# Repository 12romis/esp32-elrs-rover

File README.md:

# ESP32-ELRS-Rover

Ровер на ESP32-S3 (YD-ESP32-S3 N16R8) з керуванням через ExpressLRS/CRSF. ESP-IDF v6.1, C. Танковий привід: два борти по два колеса,
енкодери на кожному колесі, регулятор швидкості бортів, чотири далекоміри VL53L0X, світло, зумер, вбудований RGB-індикатор плати.

## Що вміє ровер

- Їде за правим стіком пульта (тяга й поворот), озброюється тумблером (канал 5), тримає швидкість бортів регулятором.
- Зупиняється при втраті звʼязку довше за 0.5 с, при напрузі акумулятора нижче 6.0 В і перед перешкодою (стан OBSTACLE_HOLD).
- Повертає на пульт напругу акумулятора (телеметрія) і показує стан утримання звуком, кольором індикатора й блиманням світла.
- Тумблер CH9 вмикає й вимикає контроль перешкод; зеленуватий індикатор плати показує, що контроль ввімкнений і реально охороняє.
- Після кожної сесії (озброєння → вихід з руху) надсилає на сервер власника звіт (JSON, MQTT поверх TLS) лише в DISARMED; невдалі
  звіти (до двох) зберігаються в пам'яті плати.
- Консоль через USB: стан, команди руху (стендовий режим), світло, зумер, енкодери, регулятор, далекоміри, звіти.

## Структура репозиторію

- `docs/` — контекст заліза й прошивки (`01-ASSEMBLY-BRINGUP.md`, `02-FIRMWARE-CONTEXT.md`), конституція (`constitution.md`),
  журнал вимірювань (`measured.md`), блок-схема (`architecture.md`), чекліст самоперевірки (`self-check.md`), дорожня карта
  (`roadmap.md`), специфікації фаз у `docs/features/<фаза>/`.
- `kicad-rover/` — схема й плата (лише читання).
- `main/`, `components/` — прошивка. Кожен компонент ділиться на `<name>_core.c` (чиста логіка, без ESP-IDF) і `<name>_hal.c`.
- `test/host/` — хостові тести чистої логіки і перевірки правил проєкту.
- `tools/bringup/` — діагностичні прошивки P0–P7 (результати — у `docs/measured.md`).

Усі номери ліній GPIO — лише в `components/board/include/board_pins.h`.

## Збірка, прошивка, тести

Збірка (потрібне середовище ESP-IDF v6.1):

```bash
source ~/.espressif/tools/activate_idf_v6.1.sh
idf.py build
```

Прошивку на плату робить Розробник через розширення ESP-IDF у VS Code (ціль `esp32s3`); агент лише збирає. Після прошивки відкрити
монітор, консоль відповідає на `help`.

Хостові тести й перевірки правил (звичайний gcc, без плати):

```bash
test/host/run_tests.sh
```

Опис перевірок — у `test/host/README.md`. Перевірки з правками захищених файлів на гілці фази: `ALLOW_PROTECTED=1 test/host/check_protected.sh`.

## Інтерфейси

### Консоль (USB)

Повний список — команда `help`. Права команд залежать від стану автомата (`status` показує стан і історію переходів).

| Команда | Призначення |
|---|---|
| `help`, `status` | довідка; стан, час роботи, пам'ять, причина скидання, сховище, світло, індикатор, пульт, **час кроку керування**, енкодери, історія переходів |
| `arm`, `drive <тяга> <поворот>` | озброєння і рух (`drive` діє 2 с) — з консолі лише в стендовому режимі, до появи пульта |
| `disarm` | роззброєння — у будь-якому стані |
| `light`, `beep` | світло й зумер: `light` у DISARMED (в ARMED лише `light head`), `beep` у DISARMED і ARMED; в OBSTACLE_HOLD обидві відхиляються |
| `enc [reset]` | знімок енкодерів |
| `pid ...` | регулятор швидкості бортів |
| `tof [reinit]` | далекоміри, сектори, поріг; `reinit` лише в DISARMED |
| `report` | звіти сесій: черга (до двох), режим контролю перешкод, мережа; у DISARMED запускає спробу передачі негайно, в інших станах лише показує стан. Пароль і SSID не друкуються: «задано / не задано» |
| `reboot`, `wdt-test` | службові (лише в безпечних станах) |

### Пульт

Канали CRSF: 1 — поворот, 2 — тяга, 5 — ARM/DISARM (тумблер), **9 — режим контролю перешкод** (див. нижче), 8 — трипозиційний перемикач, за P5 призначений під фари (у прошивці поки не використовується; докладно: `docs/02-FIRMWARE-CONTEXT.md` §1.3 і `docs/measured.md`).

**CH9 — контроль перешкод.** Значення каналу вище середини (> 992) — контроль **увімкнено**, інакше — **вимкнено** (далекоміри лише міряють,
ровер не зупиняється перед перешкодою; відсічка по напрузі, втрата зв'язку, STBY, I²C діють без змін). Поки пульт не передав
кадр або зв'язок втрачено — контроль **увімкнено** (`status` пише «за замовчуванням, пульт не підтвердив»). У мікшері EdgeTX
виведіть вибраний тумблер (SB, SC, SE чи SF) на канал CH9. Два положення цього тумблера **ще не виміряні**: Розробник записує їх у
`docs/measured.md` (spec OQ-6); до заміру канал без призначеного тумблера стоїть на 992 і вимикає захист.

### Телеметрія на пульт

Раз на 200 мс ровер надсилає кадр датчика батареї CRSF: **напруга з розв'язністю 0.1 В**. **Струм, ємність і відсоток заряду нульові
й означають «немає даних»** (датчиків немає): пульт може показувати «0 А» чи «0 %» — це не вимір. Якщо свіжого виміру напруги немає,
кадр не надсилається. На пульті датчик має знайтися автоматично (на модулі передавача співвідношення телеметрії не «вимкнено»).

### Індикація станів

| Стан | Зумер | Індикатор плати | Світло |
|---|---|---|---|
| DISARMED | короткий сигнал на вході | **зеленуватий**, якщо контроль перешкод ввімкнений і хоч один далекомір охороняє; інакше погашений | задні ліхтарі червоні, фари вручну |
| ARMED | короткий сигнал на вході | те саме (зеленуватий лише за ввімкненого контролю й охорони) | фари автоматично, задні ліхтарі: жовтий уперед, зелений назад |
| OBSTACLE_HOLD | подвійний біп на вході; на виході в ARMED — один сигнал 200 мс | **жовтий** | передній сектор зайнятий — блимають фари; задній — блимають задні ліхтарі |
| FAILSAFE | сигнал на вході, писк кожні 2 с | червоний | задні ліхтарі блимають червоним |

Пріоритет кольорів: червоний (FAILSAFE) > жовтий (OBSTACLE_HOLD) > зеленуватий > погашений. У BOOT, SELFTEST і FAULT індикатор
погашений. Консоль при вході в утримання називає **кожен** датчик сектора, що бачить перешкоду, з відстанню.

### Звіт сесії

Сесія — від озброєння до виходу з ARMED/OBSTACLE_HOLD у DISARMED чи FAILSAFE. Після неї ровер у DISARMED вмикає Wi-Fi лише на
коротку спробу (до 30 с), публікує один JSON-звіт на сервер (`rover/<mac>/session`, QoS 1) і одразу вимикає Wi-Fi. Озброєння
перериває спробу. Якщо доставити не вдалось, до двох останніх звітів лежать у пам'яті плати (переживають перезапуск, зокрема FAILSAFE
через напругу) і йдуть при наступному DISARMED або командою `report`. Поля звіту — [contracts/events.md](docs/features/phase8-session-report/contracts/events.md).

Налаштування мережі (**секрети не потрапляють у git**):

1. Скопіюйте `components/report/report_secrets.example.h` у `components/report/report_secrets.h` (файл у `.gitignore`) і заповніть
   SSID та пароль Wi-Fi, адресу й порт сервера (8883), ім'я користувача й пароль сервера. Пароль із чату вважайте скомпрометованим.
2. Покладіть кореневий сертифікат власника в `components/report/certs/root_ca.pem` (публічний, може бути в git). Дані не
   надсилаються без перевірки сертифіката сервера.
3. Після появи файлів виконайте `idf.py fullclean`. Без них збірка проходить, а передача вимкнена з одним поясненням у журналі.

Після оновлення `sdkconfig.defaults` (більший розділ застосунку, lwip на core 0) видаліть згенерований `sdkconfig` і зберіть та прошийте
заново — таблиця розділів змінюється (NVS лишається на місці).

### Відомі обмеження звіту сесії

- TP3 під Wi-Fi **не виміряно** (spec OQ-5): до заміру спроби передачі проводьте на повному акумуляторі чи живленні, що тримає межу.
- Положення CH9 на TX12 **не виміряні** (spec OQ-6, див. вище).
- Час підключення Wi-Fi і TLS, тривалість запису в пам'ять, вплив на `crc_fail` приймача **не виміряні** — чекліст приймання:
  [acceptance.md](docs/features/phase8-session-report/acceptance.md).
- Абсолютного часу немає: звіти без дат, сервер ставить мітку отримання.
- Пробіг рахується за лічильниками коліс при діаметрі 44 мм; проковзування не враховано.
## Безпека

Інваріанти (конституція, п. 7): STBY піднімається тільки в стані руху й свідомо; втрата кадрів CRSF довше за 0.5 с — ШІМ у нуль і
STBY вниз; перша операція на шині I²C — запис нуля в розширювач; напруга нижче 6.0 В — мотори не запускаються. Телеметрія й індикація
їх не змінюють і не затримують керування.

## Статус перевірки

Що перевірено на залізі, а що ні, — у `docs/self-check.md`. Приймання на залізі записує Розробник.

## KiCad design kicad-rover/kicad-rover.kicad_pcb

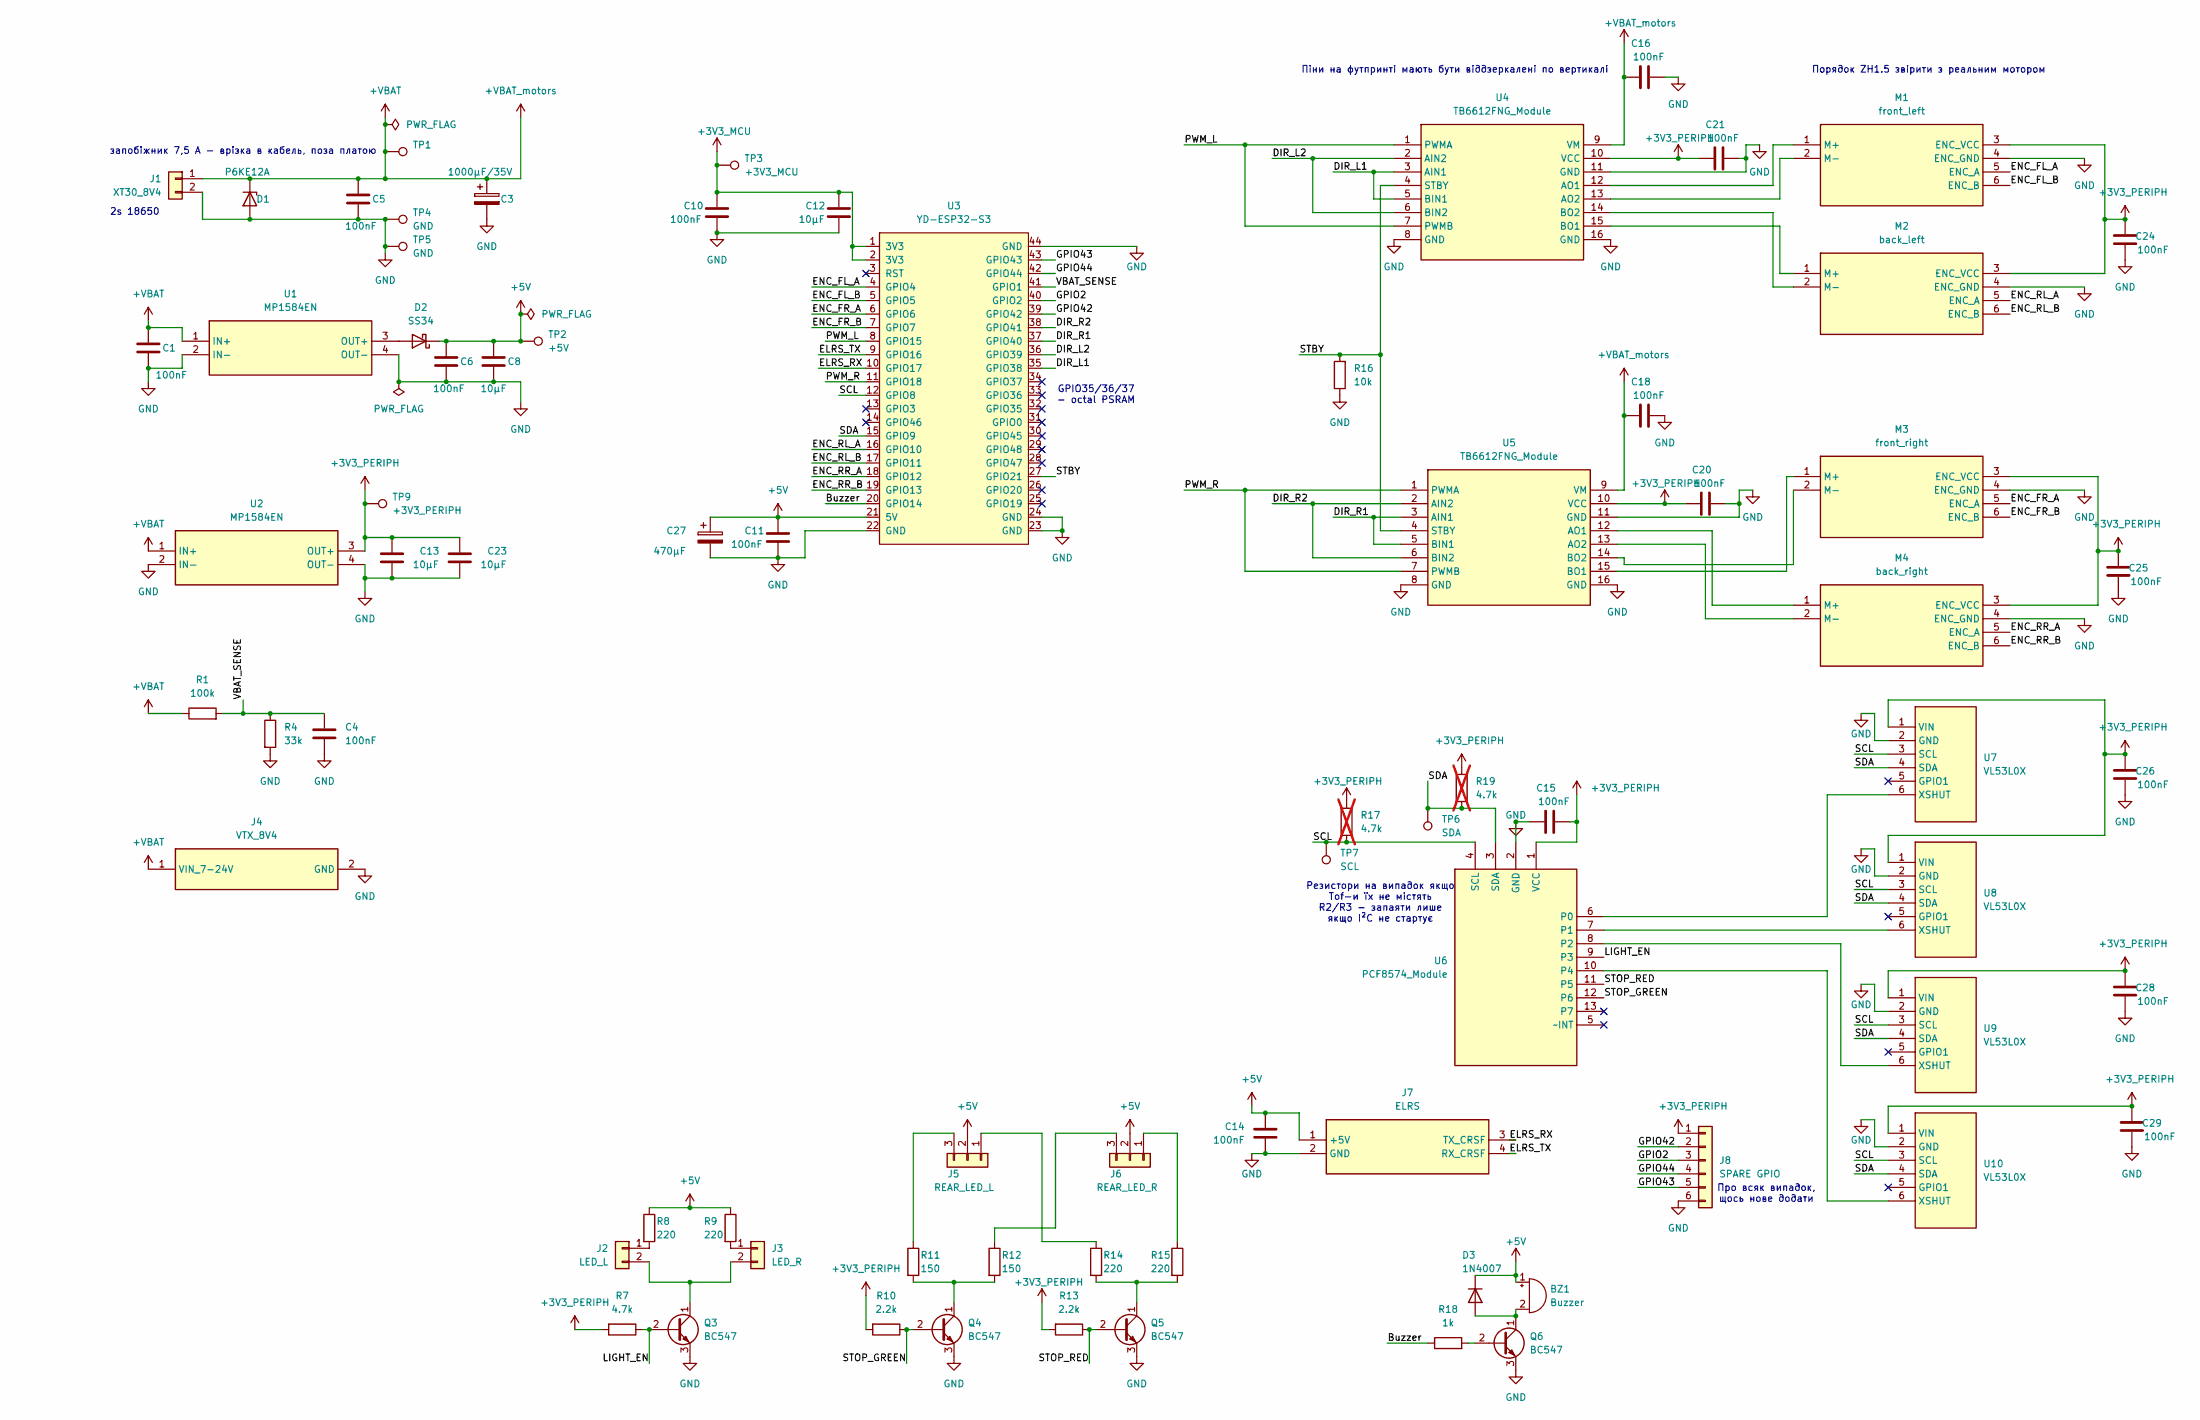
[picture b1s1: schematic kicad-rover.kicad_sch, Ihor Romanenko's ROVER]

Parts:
BZ1: Buzzer; Buzzer_12x9.5RM7.6
C1, C4, C5, C6, C10, C11, C14, C15, C16, C18, C20, C21, C24, C25, C26, C28, C29: 100nF; C_Disc_D5.0mm_W2.5mm_P5.00mm
C3: 1000µF/35V; CP_Radial_D12.5mm_P5.00mm
C8, C12, C13, C23: 10µF; C_0805_2012Metric
C27: 470µF; CP_Radial_D12.5mm_P5.00mm
D1: P6KE12A; D_DO-15_P12.70mm_Horizontal
D2: SS34; D_SMA
D3: 1N4007; D_DO-41_SOD81_P10.16mm_Horizontal
J1: XT30_8V4; SolderWire-2.5sqmm_1x02_P8.8mm_D2.4mm_OD4.4mm
J2: LED_L; JST_PH_B2B-PH-K_1x02_P2.00mm_Vertical
J3: LED_R; JST_PH_B2B-PH-K_1x02_P2.00mm_Vertical
J4: VTX_8V4; JST_PH_B2B-PH-K_1x02_P2.00mm_Vertical
J5: REAR_LED_L; JST_PH_B3B-PH-K_1x03_P2.00mm_Vertical
J6: REAR_LED_R; JST_PH_B3B-PH-K_1x03_P2.00mm_Vertical
J7: ELRS; JST_PH_B4B-PH-K_1x04_P2.00mm_Vertical
J8: SPARE GPIO; PinHeader_1x06_P2.54mm_Vertical
M1: front_left; JST_PH_B6B-PH-K_1x06_P2.00mm_Vertical
M2: back_left; JST_PH_B6B-PH-K_1x06_P2.00mm_Vertical
M3: front_right; JST_PH_B6B-PH-K_1x06_P2.00mm_Vertical
M4: back_right; JST_PH_B6B-PH-K_1x06_P2.00mm_Vertical
Q3, Q4, Q5, Q6: BC547; TO-92_Inline
R1: 100k; R_Axial_DIN0207_L6.3mm_D2.5mm_P7.62mm_Horizontal
R4: 33k; R_Axial_DIN0207_L6.3mm_D2.5mm_P7.62mm_Horizontal
R7: 4.7k; R_Axial_DIN0207_L6.3mm_D2.5mm_P7.62mm_Horizontal
R8, R9, R14, R15: 220; R_Axial_DIN0207_L6.3mm_D2.5mm_P7.62mm_Horizontal
R10, R13: 2.2k; R_Axial_DIN0207_L6.3mm_D2.5mm_P7.62mm_Horizontal
R11, R12: 150; R_Axial_DIN0207_L6.3mm_D2.5mm_P7.62mm_Horizontal
R16: 10k; R_Axial_DIN0207_L6.3mm_D2.5mm_P7.62mm_Horizontal
R17, R19: 4.7k; R_Axial_DIN0207_L6.3mm_D2.5mm_P7.62mm_Horizontal; not fitted
R18: 1k; R_Axial_DIN0207_L6.3mm_D2.5mm_P7.62mm_Horizontal
TP1: +VBAT; TestPoint_THTPad_D1.5mm_Drill0.7mm
TP2: +5V; TestPoint_THTPad_D1.5mm_Drill0.7mm
TP3: +3V3_MCU; TestPoint_THTPad_D1.5mm_Drill0.7mm
TP4, TP5: GND; TestPoint_THTPad_D1.5mm_Drill0.7mm
TP6: SDA; TestPoint_THTPad_D1.5mm_Drill0.7mm
TP7: SCL; TestPoint_THTPad_D1.5mm_Drill0.7mm
TP9: +3V3_PERIPH; TestPoint_THTPad_D1.5mm_Drill0.7mm
U1, U2: MP1584EN; MP1584EN_Module
U3: YD-ESP32-S3
U4, U5: TB6612FNG_Module
U6: PCF8574_Module; PCF8574_IO_Expansion_Module_1
U7, U8, U9, U10: VL53L0X; JST_PH_B6B-PH-K_1x06_P2.00mm_Vertical

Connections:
+3V3_MCU: C10.2, C12.2, TP3.1 (1_1), U3.1 (3V3), U3.2 (3V3)
+3V3_PERIPH: C13.2, C15.1, C20.2, C21.2, C23.2, C24.2, C25.2, C26.2, C28.2, C29.2, J8.1, M1.3 (ENC_VCC), M2.3 (ENC_VCC), M3.3 (ENC_VCC), M4.3 (ENC_VCC), R7.2, R10.2, R13.2, R17.1, R19.1, TP9.1 (1_1), U2.3 (OUT+), U4.10 (VCC), U5.10 (VCC), U6.1 (VCC), U7.1 (VIN), U8.1 (VIN), U9.1 (VIN), U10.1 (VIN)
+5V: BZ1.1 (+), C6.2, C8.2, C11.2, C14.2, C27.1, D2.1 (K), D3.1 (K), J5.2, J6.2, J7.1 (+5V), R8.1, R9.1, TP2.1 (1_1), U3.21 (5V)
+VBAT: C1.2, C3.1, C5.2, C16.2, C18.2, D1.1 (K), J1.1, J4.1 (VIN_7-24V), R1.1, TP1.1 (1_1), U1.1 (IN+), U2.1 (IN+), U4.9 (VM), U5.9 (VM)
/Buzzer: R18.1, U3.20 (GPIO14)
/DIR_L1: U3.35 (GPIO38), U4.3 (AIN1), U4.5 (BIN1)
/DIR_L2: U3.36 (GPIO39), U4.2 (AIN2), U4.6 (BIN2)
/DIR_R1: U3.37 (GPIO40), U5.3 (AIN1), U5.5 (BIN1)
/DIR_R2: U3.38 (GPIO41), U5.2 (AIN2), U5.6 (BIN2)
/ELRS_RX: J7.3 (TX_CRSF), U3.10 (GPIO17)
/ELRS_TX: J7.4 (RX_CRSF), U3.9 (GPIO16)
/ENC_FL_A: M1.5 (ENC_A), U3.4 (GPIO4)
/ENC_FL_B: M1.6 (ENC_B), U3.5 (GPIO5)
/ENC_FR_A: M3.5 (ENC_A), U3.6 (GPIO6)
/ENC_FR_B: M3.6 (ENC_B), U3.7 (GPIO7)
/ENC_RL_A: M2.5 (ENC_A), U3.16 (GPIO10)
/ENC_RL_B: M2.6 (ENC_B), U3.17 (GPIO11)
/ENC_RR_A: M4.5 (ENC_A), U3.18 (GPIO12)
/ENC_RR_B: M4.6 (ENC_B), U3.19 (GPIO13)
/GPIO2: J8.3, U3.40 (GPIO2)
/GPIO42: J8.2, U3.39 (GPIO42)
/GPIO43: J8.5, U3.43 (GPIO43)
/GPIO44: J8.4, U3.42 (GPIO44)
/LIGHT_EN: Q3.2 (B), R7.1, U6.9 (P3)
/PWM_L: U3.8 (GPIO15), U4.1 (PWMA), U4.7 (PWMB)
/PWM_R: U3.11 (GPIO18), U5.1 (PWMA), U5.7 (PWMB)
/SCL: R17.2, TP7.1 (1_1), U3.12 (GPIO8), U6.4 (SCL), U7.3 (SCL), U8.3 (SCL), U9.3 (SCL), U10.3 (SCL)
/SDA: R19.2, TP6.1 (1_1), U3.15 (GPIO9), U6.3 (SDA), U7.4 (SDA), U8.4 (SDA), U9.4 (SDA), U10.4 (SDA)
/STBY: R16.2, U3.27 (GPIO21), U4.4 (STBY), U5.4 (STBY)
/STOP_GREEN: Q4.2 (B), R10.1, U6.12 (P6)
/STOP_RED: Q5.2 (B), R13.1, U6.11 (P5)
/VBAT_SENSE: C4.2, R1.2, R4.1, U3.41 (GPIO1)
GND: C1.1, C3.2, C4.1, C5.1, C6.1, C8.1, C10.1, C11.1, C12.1, C13.1, C14.1, C15.2, C16.1, C18.1, C20.1, C21.1, C23.1, C24.1, C25.1, C26.1, C27.2, C28.1, C29.1, D1.2 (A), J1.2, J4.2 (GND), J7.2 (GND), J8.6, M1.4 (ENC_GND), M2.4 (ENC_GND), M3.4 (ENC_GND), M4.4 (ENC_GND), Q3.3 (E), Q4.3 (E), Q5.3 (E), Q6.3 (E), R4.2, R16.1, TP4.1 (1_1), TP5.1 (1_1), U1.2 (IN-), U1.4 (OUT-), U2.2 (IN-), U2.4 (OUT-), U3.22 (GND), U3.23 (GND), U3.24 (GND), U3.44 (GND), U4.8 (GND), U4.11 (GND), U4.16 (GND), U5.8 (GND), U5.11 (GND), U5.16 (GND), U6.2 (GND), U7.2 (GND), U8.2 (GND), U9.2 (GND), U10.2 (GND)
unnamed: BZ1.2 (-), D3.2 (A), Q6.1 (C)
unnamed: D2.2 (A), U1.3 (OUT+)
unnamed: J2.1, R8.2
unnamed: J2.2, J3.2, Q3.1 (C)
unnamed: J3.1, R9.2
unnamed: J5.1, R14.1
unnamed: J5.3, R11.1
unnamed: J6.1, R15.1
unnamed: J6.3, R12.1
unnamed: M1.1 (M+), U4.12 (AO1)
unnamed: M1.2 (M-), U4.13 (AO2)
unnamed: M2.1 (M+), U4.15 (BO1)
unnamed: M2.2 (M-), U4.14 (BO2)
unnamed: M3.1 (M+), U5.15 (BO1)
unnamed: M3.2 (M-), U5.14 (BO2)
unnamed: M4.1 (M+), U5.12 (AO1)
unnamed: M4.2 (M-), U5.13 (AO2)
unnamed: Q4.1 (C), R11.2, R12.2
unnamed: Q5.1 (C), R14.2, R15.2
unnamed: Q6.2 (B), R18.2
unnamed: U6.6 (P0), U7.6 (XSHUT)
unnamed: U6.7 (P1), U8.6 (XSHUT)
unnamed: U6.8 (P2), U9.6 (XSHUT)
unnamed: U6.10 (P4), U10.6 (XSHUT)

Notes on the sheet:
Порядок ZH1.5 звірити з реальним мотором
Піни на футпринті мають бути віддзеркалені по вертикалі
GPIO35/36/37 - octal PSRAM
2s 18650
запобіжник 7,5 А - врізка в кабель, поза платою
Про всяк випадок, щось нове додати
Резистори на випадок якщо Tof-и їх не містять R2/R3 - запаяти лише якщо I²C не стартує

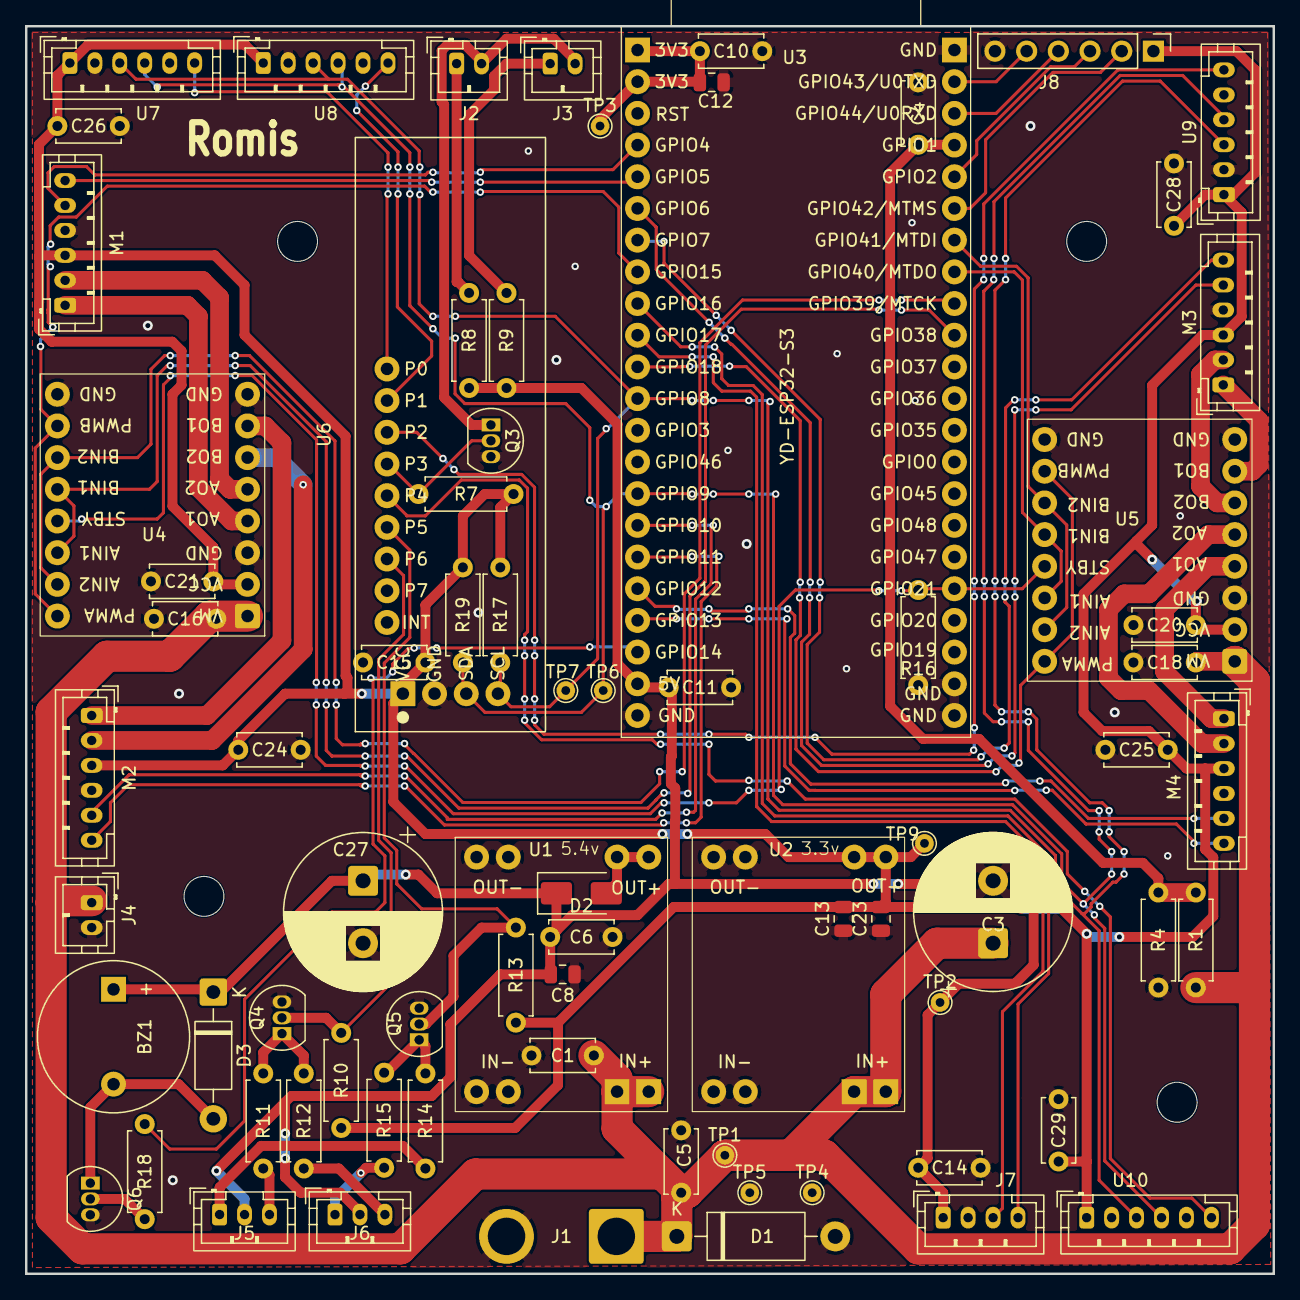
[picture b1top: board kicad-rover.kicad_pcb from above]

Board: 2 copper layers, 100.0 x 100.0 mm, 80 parts (0 on the bottom side), 57 nets.

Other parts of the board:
H1, H2, H3, H4: MountingHole_3.2mm_M3

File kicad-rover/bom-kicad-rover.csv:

"Reference","Qty","Value","DNP","Exclude from BOM","Exclude from Board","Exclude from Simulation","Exclude from Position Files","Footprint","Datasheet"
"BZ1","1","Buzzer","","","","","${EXCLUDE_FROM_POS_FILES}","Buzzer_Beeper:Buzzer_12x9.5RM7.6",""
"C1,C4,C5,C6,C10,C11,C14,C15,C16,C18,C20,C21,C24,C25,C26,C28,C29","17","100nF","","","","","${EXCLUDE_FROM_POS_FILES}","Capacitor_THT:C_Disc_D5.0mm_W2.5mm_P5.00mm",""
"C3","1","1000µF/35V","","","","","${EXCLUDE_FROM_POS_FILES}","Capacitor_THT:CP_Radial_D12.5mm_P5.00mm",""
"C8,C12,C13,C23","4","10µF","","","","","${EXCLUDE_FROM_POS_FILES}","Capacitor_SMD:C_0805_2012Metric",""
"C27","1","470µF","","","","","${EXCLUDE_FROM_POS_FILES}","Capacitor_THT:CP_Radial_D12.5mm_P5.00mm",""
"D1","1","P6KE12A","","","","","${EXCLUDE_FROM_POS_FILES}","Diode_THT:D_DO-15_P12.70mm_Horizontal",""
"D2","1","SS34","","","","","${EXCLUDE_FROM_POS_FILES}","Diode_SMD:D_SMA",""
"D3","1","1N4007","","","","","${EXCLUDE_FROM_POS_FILES}","Diode_THT:D_DO-41_SOD81_P10.16mm_Horizontal","http://www.vishay.com/docs/88503/1n4001.pdf"
"J1","1","XT30_8V4","","","","","${EXCLUDE_FROM_POS_FILES}","Connector_Wire:SolderWire-2.5sqmm_1x02_P8.8mm_D2.4mm_OD4.4mm",""
"J2","1","LED_L","","","","","${EXCLUDE_FROM_POS_FILES}","Connector_JST:JST_PH_B2B-PH-K_1x02_P2.00mm_Vertical",""
"J3","1","LED_R","","","","","${EXCLUDE_FROM_POS_FILES}","Connector_JST:JST_PH_B2B-PH-K_1x02_P2.00mm_Vertical",""
"J4","1","VTX_8V4","","","","","${EXCLUDE_FROM_POS_FILES}","Connector_JST:JST_PH_B2B-PH-K_1x02_P2.00mm_Vertical",""
"J5","1","REAR_LED_L","","","","","${EXCLUDE_FROM_POS_FILES}","Connector_JST:JST_PH_B3B-PH-K_1x03_P2.00mm_Vertical",""
"J6","1","REAR_LED_R","","","","","${EXCLUDE_FROM_POS_FILES}","Connector_JST:JST_PH_B3B-PH-K_1x03_P2.00mm_Vertical",""
"J7","1","ELRS","","","","","${EXCLUDE_FROM_POS_FILES}","Connector_JST:JST_PH_B4B-PH-K_1x04_P2.00mm_Vertical",""
"J8","1","SPARE GPIO","","","","","${EXCLUDE_FROM_POS_FILES}","Connector_PinHeader_2.54mm:PinHeader_1x06_P2.54mm_Vertical",""
"M1","1","front_left","","","","","${EXCLUDE_FROM_POS_FILES}","Connector_JST:JST_PH_B6B-PH-K_1x06_P2.00mm_Vertical",""
"M2","1","back_left","","","","","${EXCLUDE_FROM_POS_FILES}","Connector_JST:JST_PH_B6B-PH-K_1x06_P2.00mm_Vertical",""
"M3","1","front_right","","","","","${EXCLUDE_FROM_POS_FILES}","Connector_JST:JST_PH_B6B-PH-K_1x06_P2.00mm_Vertical",""
"M4","1","back_right","","","","","${EXCLUDE_FROM_POS_FILES}","Connector_JST:JST_PH_B6B-PH-K_1x06_P2.00mm_Vertical",""
"Q3,Q4,Q5,Q6","4","BC547","","","","","${EXCLUDE_FROM_POS_FILES}","Package_TO_SOT_THT:TO-92_Inline",""
"R1","1","100k","","","","","${EXCLUDE_FROM_POS_FILES}","Resistor_THT:R_Axial_DIN0207_L6.3mm_D2.5mm_P7.62mm_Horizontal",""
"R4","1","33k","","","","","${EXCLUDE_FROM_POS_FILES}","Resistor_THT:R_Axial_DIN0207_L6.3mm_D2.5mm_P7.62mm_Horizontal",""
"R7","1","4.7k","","","","","${EXCLUDE_FROM_POS_FILES}","Resistor_THT:R_Axial_DIN0207_L6.3mm_D2.5mm_P7.62mm_Horizontal",""
"R8,R9,R14,R15","4","220","","","","","${EXCLUDE_FROM_POS_FILES}","Resistor_THT:R_Axial_DIN0207_L6.3mm_D2.5mm_P7.62mm_Horizontal",""
"R10,R13","2","2.2k","","","","","${EXCLUDE_FROM_POS_FILES}","Resistor_THT:R_Axial_DIN0207_L6.3mm_D2.5mm_P7.62mm_Horizontal",""
"R11,R12","2","150","","","","","${EXCLUDE_FROM_POS_FILES}","Resistor_THT:R_Axial_DIN0207_L6.3mm_D2.5mm_P7.62mm_Horizontal",""
"R16","1","10k","","","","","${EXCLUDE_FROM_POS_FILES}","Resistor_THT:R_Axial_DIN0207_L6.3mm_D2.5mm_P7.62mm_Horizontal",""
"R17,R19","2","4.7k","DNP","","","","${EXCLUDE_FROM_POS_FILES}","Resistor_THT:R_Axial_DIN0207_L6.3mm_D2.5mm_P7.62mm_Horizontal",""
"R18","1","1k","","","","","${EXCLUDE_FROM_POS_FILES}","Resistor_THT:R_Axial_DIN0207_L6.3mm_D2.5mm_P7.62mm_Horizontal",""
"TP1","1","+VBAT","","","","","${EXCLUDE_FROM_POS_FILES}","TestPoint:TestPoint_THTPad_D1.5mm_Drill0.7mm",""
"TP2","1","+5V","","","","","${EXCLUDE_FROM_POS_FILES}","TestPoint:TestPoint_THTPad_D1.5mm_Drill0.7mm",""
"TP3","1","+3V3_MCU","","","","","${EXCLUDE_FROM_POS_FILES}","TestPoint:TestPoint_THTPad_D1.5mm_Drill0.7mm",""
"TP4,TP5","2","GND","","","","","${EXCLUDE_FROM_POS_FILES}","TestPoint:TestPoint_THTPad_D1.5mm_Drill0.7mm",""
"TP6","1","SDA","","","","","${EXCLUDE_FROM_POS_FILES}","TestPoint:TestPoint_THTPad_D1.5mm_Drill0.7mm",""
"TP7","1","SCL","","","","","${EXCLUDE_FROM_POS_FILES}","TestPoint:TestPoint_THTPad_D1.5mm_Drill0.7mm",""
"TP9","1","+3V3_PERIPH","","","","","${EXCLUDE_FROM_POS_FILES}","TestPoint:TestPoint_THTPad_D1.5mm_Drill0.7mm",""
"U1,U2","2","MP1584EN","","","","","${EXCLUDE_FROM_POS_FILES}","rover_footprints:MP1584EN_Module",""
"U3","1","YD-ESP32-S3","","","","","${EXCLUDE_FROM_POS_FILES}","YD-ESP32-S3-main:YD-ESP32-S3",""
"U4,U5","2","TB6612FNG_Module","","","","","${EXCLUDE_FROM_POS_FILES}","rover_footprints:TB6612FNG_Module",""
"U6","1","PCF8574_Module","","","","","${EXCLUDE_FROM_POS_FILES}","rover_footprints:PCF8574_IO_Expansion_Module_1",""
"U7,U8,U9,U10","4","VL53L0X","","","","","${EXCLUDE_FROM_POS_FILES}","Connector_JST:JST_PH_B6B-PH-K_1x06_P2.00mm_Vertical",""

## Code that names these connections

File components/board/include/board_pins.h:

// Єдине місце з номерами GPIO. Джерело: kicad-rover.net, docs/02-FIRMWARE-CONTEXT.md §2.
// Це фізичні доріжки — не міняти без перерозводки.
#pragma once

// Батарея (ADC1_CH0)
#define PIN_VBAT_SENSE   1

// I²C (PCF8574, VL53L0X)
#define PIN_I2C_SCL      8
#define PIN_I2C_SDA      9

// Енкодери (PCNT units 0..3)
#define PIN_ENC_FL_A     4
#define PIN_ENC_FL_B     5
#define PIN_ENC_FR_A     6
#define PIN_ENC_FR_B     7
#define PIN_ENC_RL_A     10
#define PIN_ENC_RL_B     11
#define PIN_ENC_RR_A     12
#define PIN_ENC_RR_B     13

// Мотори (TB6612FNG ×2)
#define PIN_PWM_L        15
#define PIN_PWM_R        18
#define PIN_DIR_L1       38
#define PIN_DIR_L2       39
#define PIN_DIR_R1       40
#define PIN_DIR_R2       41
#define PIN_STBY         21   // апаратний failsafe, 0 = мотори вимкнені

// Зумер (LEDC)
#define PIN_BUZZER       14

// ELRS / CRSF (UART2)
#define PIN_ELRS_TX      16
#define PIN_ELRS_RX      17

// Резерв J8
#define PIN_J8_GPIO2     2
#define PIN_J8_GPIO42    42
#define PIN_J8_GPIO43    43
#define PIN_J8_GPIO44    44

// Вбудований RGB-індикатор модуля. Лінія — за документом 02, §2 (у нетлисті плати цього немає: світлодіод усередині модуля).
// Адресований світлодіод, порядок байтів GRB (виміряно: 2026-10-18, P8, docs/measured.md); драйвер — ADR-0005 phase2-io.
#define PIN_STATUS_RGB   48

// Біти PCF8574 (U6)
#define PCF8574_ADDR           0x20   // виміряно P1: 2026-10-16 (docs/measured.md)
#define IOEXP_BIT_XSHUT_U7     0
#define IOEXP_BIT_XSHUT_U8     1
#define IOEXP_BIT_XSHUT_U9     2
#define IOEXP_BIT_LIGHT_EN     3   // 1 = фари горять
#define IOEXP_BIT_XSHUT_U10    4   // не P3!
#define IOEXP_BIT_STOP_RED     5   // 1 = горить
#define IOEXP_BIT_STOP_GREEN   6   // 1 = горить
// P7 вільний
